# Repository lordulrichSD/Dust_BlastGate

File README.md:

# Dust_BlastGate

This project is a Dust collection system blast gate for woodworking or other dust collection.  The device provides control of a servo to actuate the blast gate, manual control of the blast gate position, a connector to attatch a sensor for tool activation and automatic control and wifi connection to activate a dust collector connected to a Kassa capable smart plug or switch.  

Software is seetup to allow over the air firmware updates direct from github. BoardInfo.py and Settings.py are not part of OTA update. BoardInfo.py contains hardware pinouts and should reflect hardware revisions.  Settings.py contains device configurations, i.e. wifi, servo limits, IP for dust collector and delay time.  These settings are set per device

BoardInfo files contain board specific information (i.e. pin mappings), BoardInfo must be loaded manualy at inital install and will not update OTA.  

Hardware folder contains KiCAD files for board revisions.  Boards are uploaded to OSHpark.  

Firmware folder contains the firmware.  Files except Settings.py are subject to OTA update.  

settings.py file contains example data/startup data. File will be overwritten when configuring board for the first time.  Write this file durring intial install.

Hardware
Hardware contains 2 main modules.  The main control module and sensor module.  
The main control module contains an ESP32 module (providing microcontroler and wifi connection).  In addition the main control module holds support hardware (i.e. power supply) and interface connections.  
A manual control switch (1p3t on-off-on) provides manual on, auto, manual off control.  
Dip switches provide for entering Access Point Mode for settings, enabling WIFI (when not in AP mode) enabling the sensor in put.  
A FTDI type 6 pin headder is provided for programing and debug by serial.
A 3 pin header is provided to connect a hobby servo to activate the physical blast gate
Sensor connection is via a RJ-9 Style connector to allow easy cable creation of needed lenght for indivitual physical install.  This connector includes 3.3v, ground, sensor data (logic high/low), and raw USB voltage (allowing USB power supply to be at sensor location)
A USB connetor is provided for power only.  A jumper or switch (populate 1) allowing selection of power source (one at a time, sensor or main control module)

(Future feature to deploy)
OTA updated based on ugit (https://github.com/turfptax/ugit)
https://github.com/turfptax/ugit/blob/f6872930eea33ae5fb45ea48af146518e4737e93/ugit.py

KASA integration based on the work by GadgetReactor in the pyHS100 based on the work of The communication protocol was reverse engineered by Lubomir Stroetmann and
Tobias Esser in 'Reverse Engineering the TP-Link HS110':
https://www.softscheck.com/en/reverse-engineering-tp-link-hs110/.  The HS100 or python-kasa libraries were not used directly due to memory limitations of the ESP32 module so only limited functions were recreated directly.

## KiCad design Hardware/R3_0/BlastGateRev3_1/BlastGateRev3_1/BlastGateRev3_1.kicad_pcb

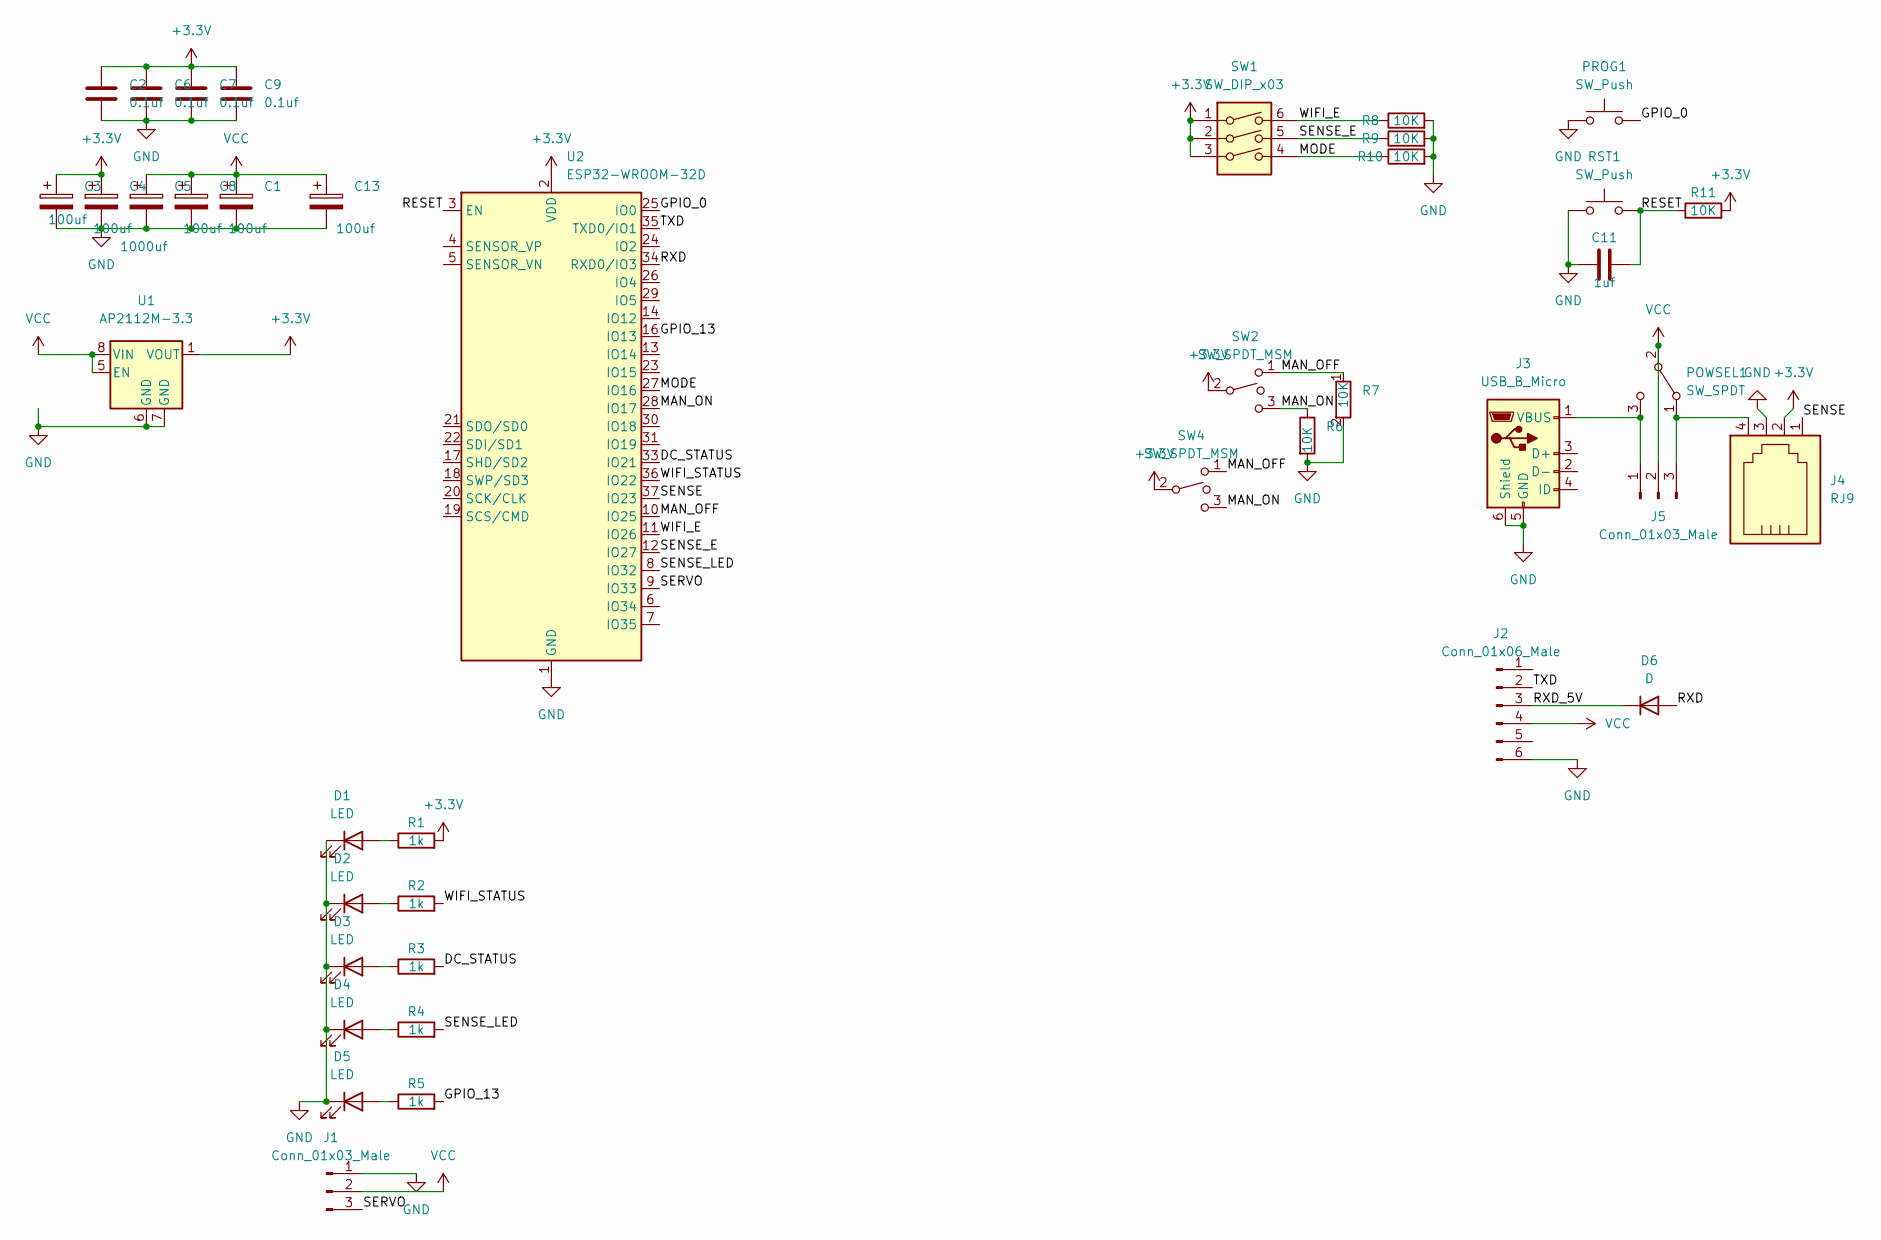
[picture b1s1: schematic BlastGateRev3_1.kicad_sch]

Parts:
C1, C3, C4, C8, C13: 100uf; CP_Radial_D5.0mm_P2.50mm
C2, C6, C7, C9: 0.1uf; C_1206_3216Metric_Pad1.33x1.80mm_HandSolder
C5: 1000uf; CP_Radial_D12.5mm_P5.00mm
C11: 1uf; C_1206_3216Metric_Pad1.33x1.80mm_HandSolder
D1, D2, D3, D4, D5: LED; LED_1206_3216Metric_Pad1.42x1.75mm_HandSolder
D6: D; D_DO-41_SOD81_P3.81mm_Vertical_AnodeUp
J1, J5: Conn_01x03_Male; PinHeader_1x03_0.1in lock
J2: Conn_01x06_Male; PinHeader_1x06, .1in Lock
J3: USB_B_Micro; usb; PartNum 54-00019T-ND
J4: RJ9; modjack; PartNum AE10381-ND
POWSEL1: SW_SPDT; EG1224
PROG1: SW_Push; pb CKN12301-ND; PartNum CKN12301-ND
R1, R2, R3, R4, R5: 1k; R_1206_3216Metric_Pad1.30x1.75mm_HandSolder
R6, R7, R8, R9, R10, R11: 10K; R_1206_3216Metric_Pad1.30x1.75mm_HandSolder
RST1: SW_Push; pb CKN12301-ND; PartNum CKN12301-ND
SW1: SW_DIP_x03; SW_DIP_SPSTx03_Slide_6.7x9.18mm_W7.62mm_P2.54mm_LowProfile; PartNum CT2103MS-ND
SW2: SW_SPDT_MSM; BST13T1AVR; PartNum 2449-BST13T1AVR-ND
SW4: SW_SPDT_MSM; 400AWMSP3R1BLKM6QE rocker; PartNum 400AWMSP3R1BLKM6QE-ND
U1: AP2112M-3.3; Diodes_SO-8EP; PartNum AP2112M-3.3TRG1DICT-ND
U2: ESP32-WROOM-32D; ESP32-WROOM-32; PartNum 1965-ESP32-WROOM-32E-H4CT-ND

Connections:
+3.3V: C2.1, C3.1, C4.1, C6.1, C7.1, C9.1, J4.2, R1.2, R11.2, SW1.1, SW1.2, SW1.3, SW2.2, SW4.2, U1.1 (VOUT), U2.2 (VDD)
/DC_STATUS: R3.2, U2.33 (IO21)
/GPIO_0: PROG1.2, U2.25 (IO0)
/GPIO_13: R5.2, U2.16 (IO13)
/MAN_OFF: R7.1, SW2.1, SW4.1, U2.10 (IO25)
/MAN_ON: R6.1, SW2.3, SW4.3, U2.28 (IO17)
/MODE: R10.1, SW1.4, U2.27 (IO16)
/RESET: C11.2, R11.1, RST1.2, U2.3 (EN)
/RXD: D6.2 (A), U2.34 (RXD0/IO3)
/RXD_5V: D6.1 (K), J2.3
/SENSE: J4.1, U2.37 (IO23)
/SENSE_E: R9.1, SW1.5, U2.12 (IO27)
/SENSE_LED: R4.2, U2.8 (IO32)
/SERVO: J1.3, U2.9 (IO33)
/TXD: J2.2, U2.35 (TXD0/IO1)
/WIFI_E: R8.1, SW1.6, U2.11 (IO26)
/WIFI_STATUS: R2.2, U2.36 (IO22)
GND: C1.2, C2.2, C3.2, C4.2, C5.2, C6.2, C7.2, C8.2, C9.2, C11.1, C13.2, D1.1 (K), D2.1 (K), D3.1 (K), D4.1 (K), D5.1 (K), J1.1, J2.6, J3.5 (GND), J3.6 (Shield), J4.3, PROG1.1, R6.2, R7.2, R8.2, R9.2, R10.2, RST1.1, U1.6 (GND), U1.7 (GND), U2.1 (GND), U2.15 (GND), U2.38 (GND), U2.39 (GND)
unnamed: D1.2 (A), R1.1
unnamed: D2.2 (A), R2.1
unnamed: D3.2 (A), R3.1
unnamed: D4.2 (A), R4.1
unnamed: D5.2 (A), R5.1
unnamed: J3.1 (VBUS), J5.1, POWSEL1.3 (C)
unnamed: J4.4, J5.3, POWSEL1.1 (A)
VCC: C1.1, C5.1, C8.1, C13.1, J1.2, J2.4, J5.2, POWSEL1.2 (B), U1.5 (EN), U1.8 (VIN)

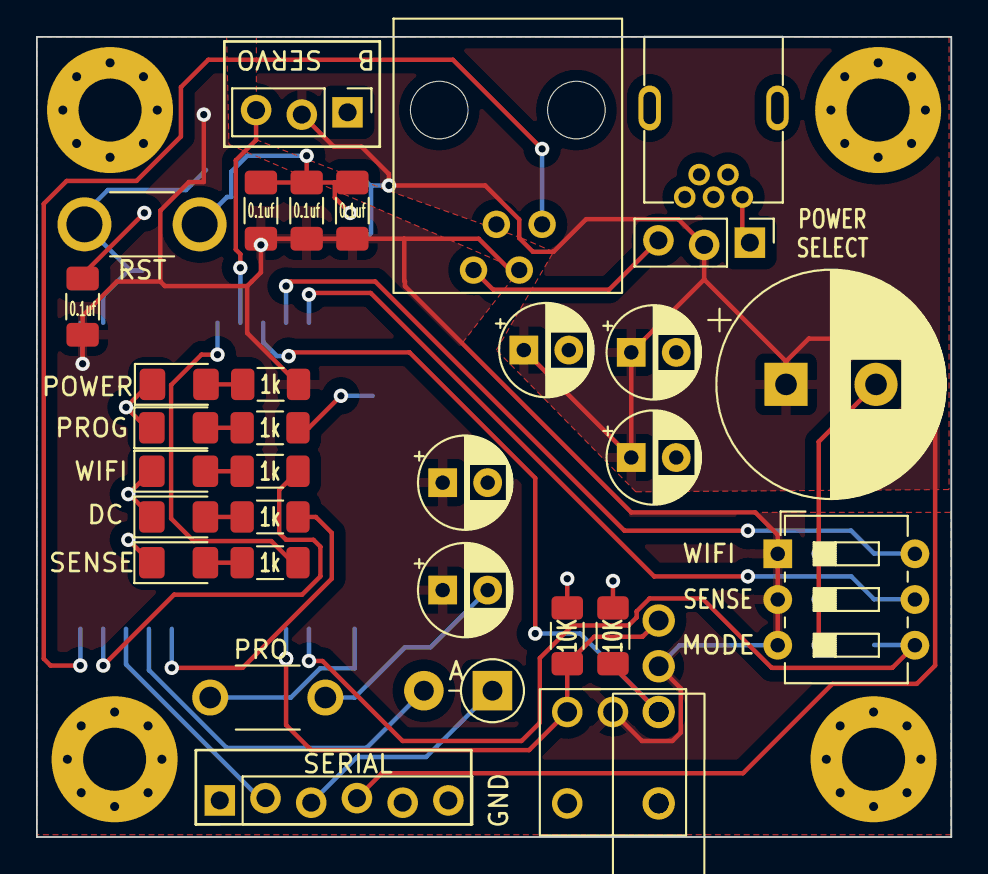
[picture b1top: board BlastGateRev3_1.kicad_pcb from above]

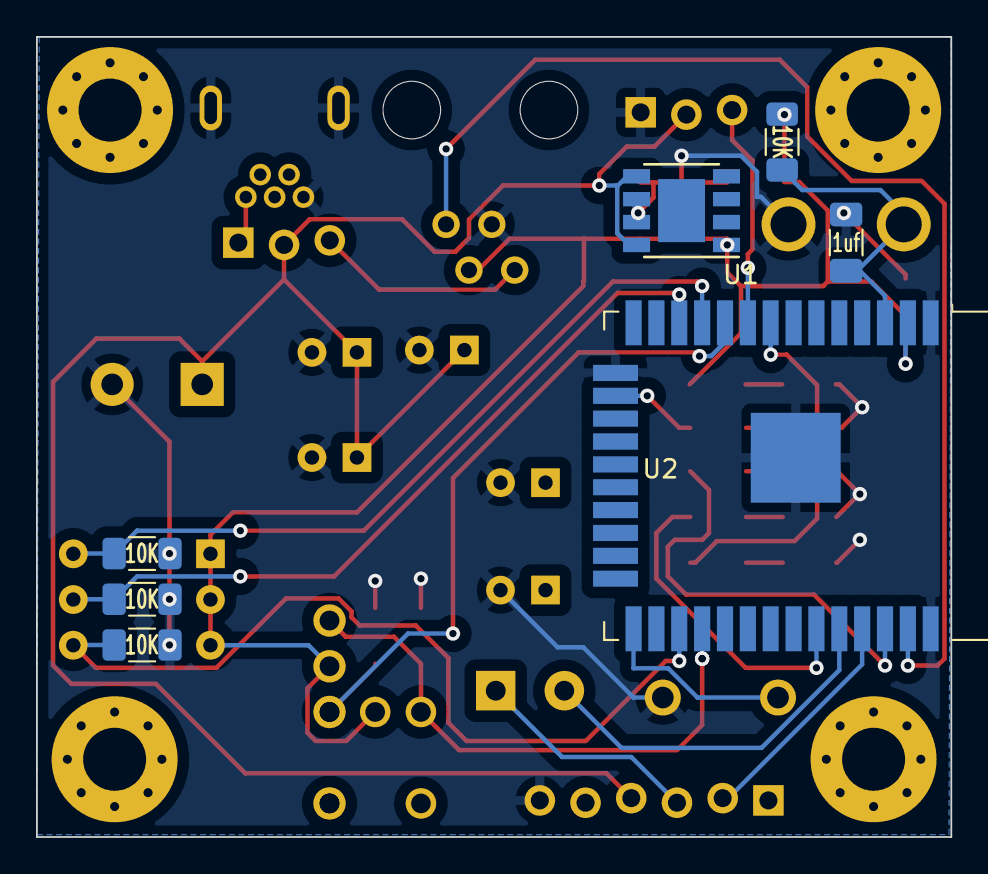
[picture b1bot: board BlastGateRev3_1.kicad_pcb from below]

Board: 2 copper layers, 50.8 x 44.5 mm, 40 parts (7 on the bottom side), 26 nets.

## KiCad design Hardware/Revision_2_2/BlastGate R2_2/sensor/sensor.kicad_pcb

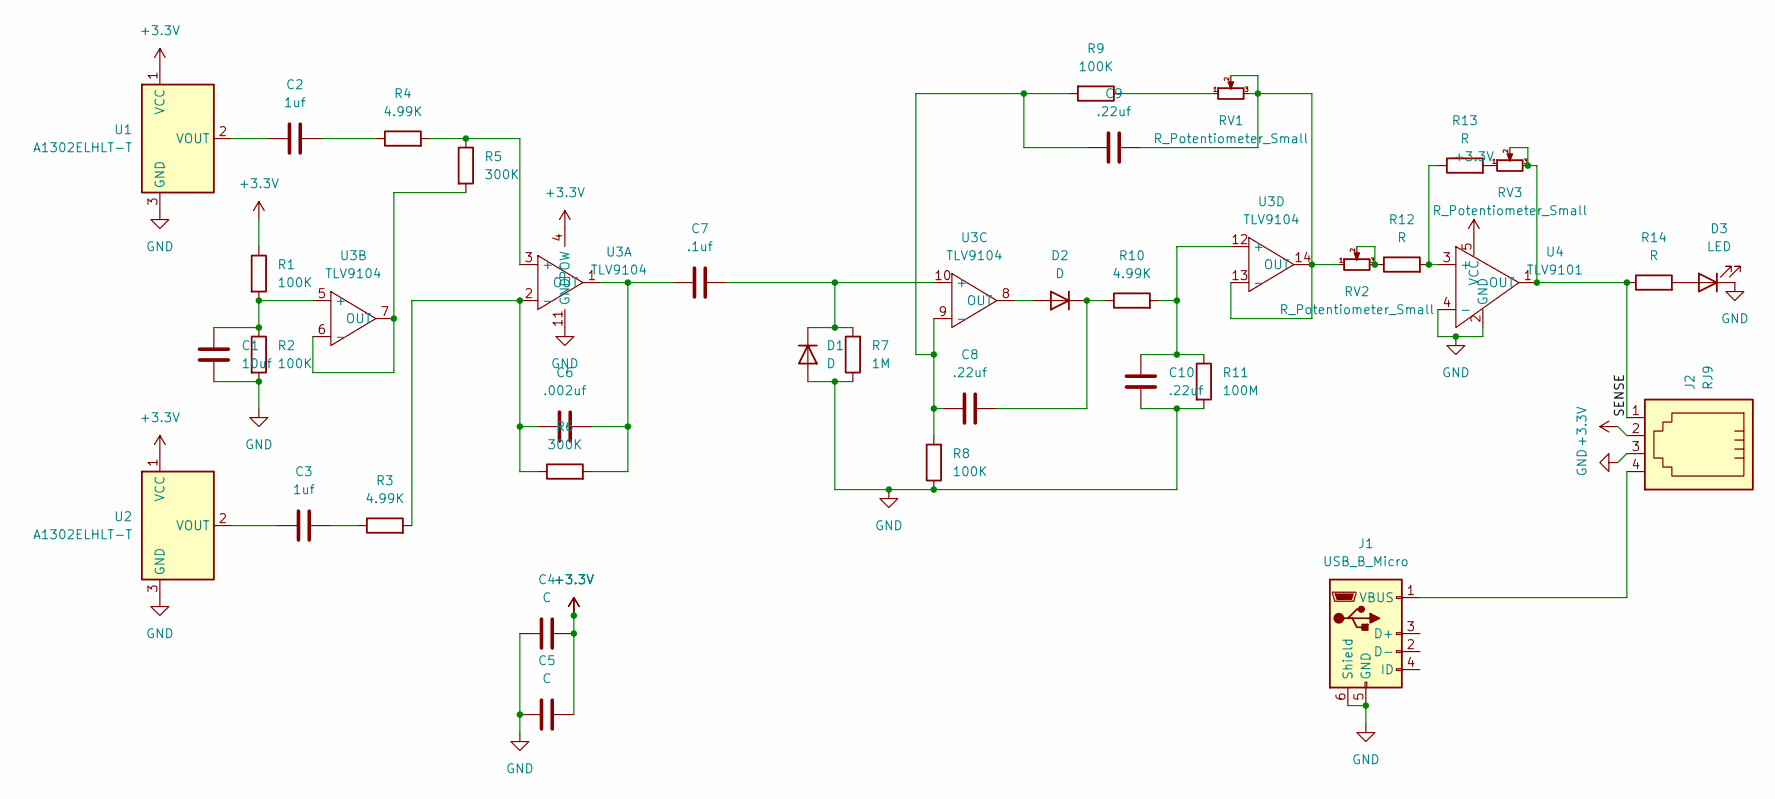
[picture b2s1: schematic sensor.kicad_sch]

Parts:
C1: 10uf; C_0805_2012Metric_Pad1.18x1.45mm_HandSolder
C2, C3: 1uf; C_0805_2012Metric_Pad1.18x1.45mm_HandSolder
C4, C5: C; C_0805_2012Metric_Pad1.18x1.45mm_HandSolder
C6: .002uf; C_0805_2012Metric_Pad1.18x1.45mm_HandSolder
C7: .1uf; C_0805_2012Metric_Pad1.18x1.45mm_HandSolder
C8, C9, C10: .22uf; C_0805_2012Metric_Pad1.18x1.45mm_HandSolder
D1, D2: D; D_SOD-123
D3: LED; LED_1206_3216Metric_Pad1.42x1.75mm_HandSolder
J1: USB_B_Micro; USB_Micro-B_Amphenol_10118194_Horizontal
J2: RJ9; modjack
R1, R2, R8, R9: 100K; R_1206_3216Metric_Pad1.30x1.75mm_HandSolder
R3, R4, R10: 4.99K; R_1206_3216Metric_Pad1.30x1.75mm_HandSolder
R5, R6: 300K; R_1206_3216Metric_Pad1.30x1.75mm_HandSolder
R7: 1M; R_1206_3216Metric_Pad1.30x1.75mm_HandSolder
R11: 100M; R_1206_3216Metric_Pad1.30x1.75mm_HandSolder
R12, R13, R14: R; R_1206_3216Metric_Pad1.30x1.75mm_HandSolder
RV1, RV2, RV3: R_Potentiometer_Small; Potentiometer_Bourns_TC33X_Vertical
U1, U2: A1302ELHLT-T; TO-92L_Inline
U3: TLV9104; TSSOP-14_4.4x5mm_P0.65mm
U4: TLV9101; SOT-353_SC-70-5_Handsoldering

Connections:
+3.3V: C4.2, C5.2, J2.2, R1.1, U1.1 (VCC), U2.1 (VCC), U3.4 (POW), U4.5 (VCC)
/SENSE: J2.1, R14.1, RV3.2, RV3.3, U4.1 (OUT)
GND: C1.2, C4.1, C5.1, C10.1, D1.2 (A), D3.1 (K), J1.5 (GND), J1.6 (Shield), J2.3, R2.2, R7.1, R8.1, R11.2, U1.3 (GND), U2.3 (GND), U3.11 (GND), U4.2 (GND), U4.4 (-)
unnamed: C1.1, R1.2, R2.1, U3.5 (+)
unnamed: C2.1, R4.1
unnamed: C2.2, U1.2 (VOUT)
unnamed: C3.1, U2.2 (VOUT)
unnamed: C3.2, R3.1
unnamed: C6.1, R3.2, R6.1, U3.2 (-)
unnamed: C6.2, C7.1, R6.2, U3.1 (OUT)
unnamed: C7.2, D1.1 (K), R7.2, U3.10 (+)
unnamed: C8.1, C9.2, R8.2, R9.2, U3.9 (-)
unnamed: C8.2, D2.1 (K), R10.1
unnamed: C9.1, RV1.2, RV1.3, RV2.1, U3.13 (-), U3.14 (OUT)
unnamed: C10.2, R10.2, R11.1, U3.12 (+)
unnamed: D2.2 (A), U3.8 (OUT)
unnamed: D3.2 (A), R14.2
unnamed: J1.1 (VBUS), J2.4
unnamed: R4.2, R5.1, U3.3 (+)
unnamed: R5.2, U3.6 (-), U3.7 (OUT)
unnamed: R9.1, RV1.1
unnamed: R12.1, RV2.2, RV2.3
unnamed: R12.2, R13.1, U4.3 (+)
unnamed: R13.2, RV3.1

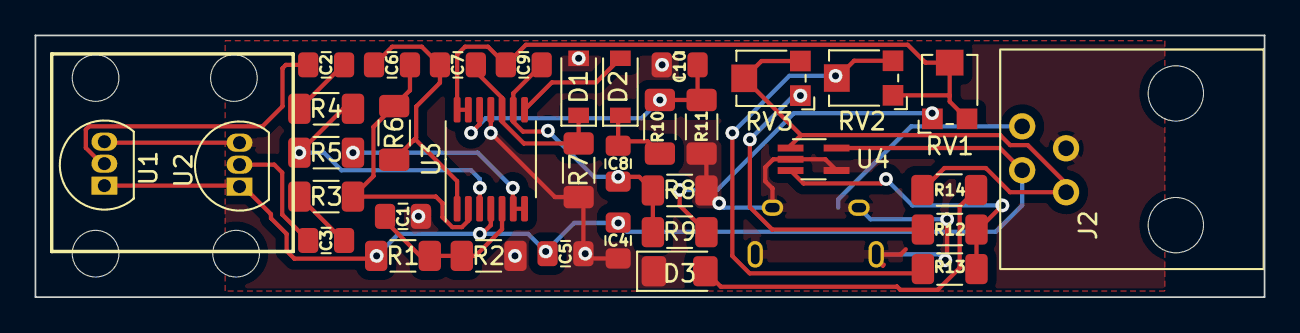
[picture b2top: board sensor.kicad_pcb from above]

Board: 2 copper layers, 71.1 x 15.1 mm, 36 parts (1 on the bottom side), 24 nets.

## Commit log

2023-01-04 Created Firmware folder
2023-01-04 Upload draft file
2023-01-05 Added Hardware Information
2023-01-05 Split to boot and main
2023-01-05 fix file names
2023-01-05 added hardware test code
2023-01-06 fix issue if wifi not enabled
2023-01-08 add servo movement to ap mode
2023-01-19 Improved turn on performance
2023-01-20 hw revisions
2023-01-28 hardware revision,
2023-01-29 Update Folder Structure
2023-03-31 Add GC, Code Cleanup
2023-03-31 Add auto reboot at Midnight
